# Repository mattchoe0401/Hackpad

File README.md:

# Hackpad
This Hackpad uses 7 keys and a rotary encoder, each programmed for different functions.

It has an OLED screen that uses global WPM (tracked by a background Python program) to determine when a Bongo Cat hits.

The keybinds are as follows:

COPY&nbsp;&nbsp;&emsp;PASTE&emsp;&nbsp;&nbsp;UP&emsp;&emsp;&emsp;&nbsp;MUTE\
CUT&emsp;&emsp;LEFT&emsp;&emsp;&nbsp;DOWN&emsp;&nbsp;&nbsp;RIGHT

Pressing down the rotary encoder mutes/unmutes, while rotating it adjusts the volume.

# CAD Model

# Schematic and PCB
Schematic:\

PCB:\

# Bill of Materials
**See hackpad_bom.csv for the list of prices and links**
- 1x Seeed XIAO RP2040
- 7x Cherry MX key switches
- 5x M3x16mm screws
- 5x M3x5mx4mm heatset inserts
- 1x EC11E rotary encoder
- 1x 0.91-inch OLED display
- 7x White DSA keycaps

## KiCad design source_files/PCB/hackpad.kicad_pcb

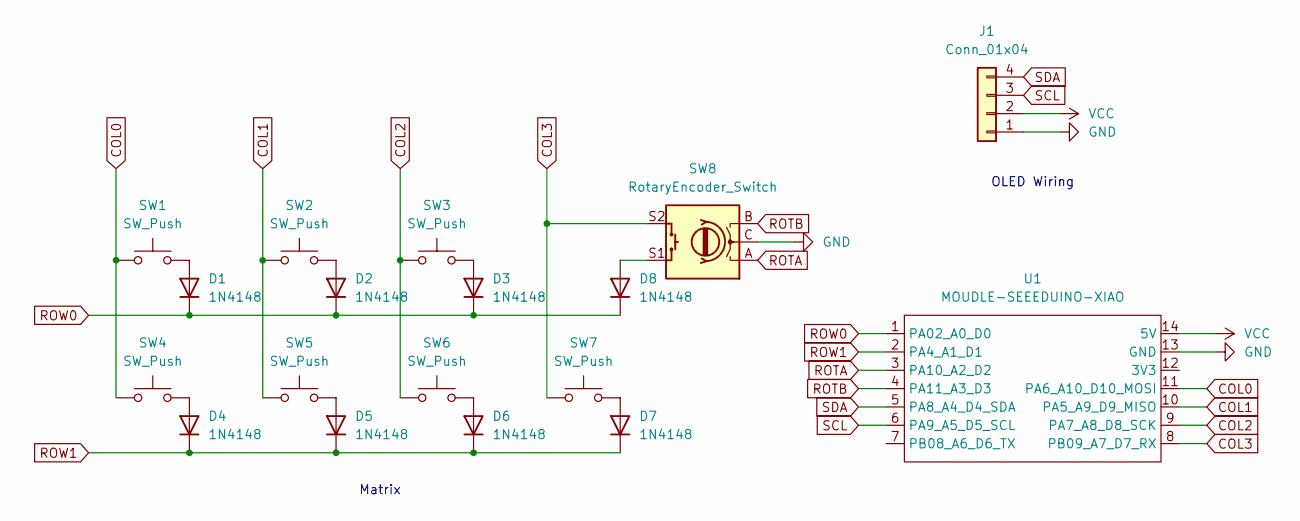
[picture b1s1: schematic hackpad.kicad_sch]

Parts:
D1, D2, D3, D4, D5, D6, D7, D8: 1N4148; D_DO-35_SOD27_P7.62mm_Horizontal
J1: Conn_01x04; SSD1306-0.91-OLED-4pin-128x32
SW1, SW2, SW3, SW4, SW5, SW6, SW7: SW_Push; SW_Cherry_MX_1.00u_PCB
SW8: RotaryEncoder_Switch; RotaryEncoder_Alps_EC11E-Switch_Vertical_H20mm
U1: MOUDLE-SEEEDUINO-XIAO; XIAO-Generic-Hybrid-14P-2.54-21X17.8MM

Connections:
COL0: SW1.1, SW4.1, U1.11 (PA6_A10_D10_MOSI)
COL1: SW2.1, SW5.1, U1.10 (PA5_A9_D9_MISO)
COL2: SW3.1, SW6.1, U1.9 (PA7_A8_D8_SCK)
COL3: SW7.1, SW8.S2, U1.8 (PB09_A7_D7_RX)
GND: J1.1, SW8.C, U1.13 (GND)
unnamed: D1.2 (A), SW1.2
unnamed: D2.2 (A), SW2.2
unnamed: D3.2 (A), SW3.2
unnamed: D4.2 (A), SW4.2
unnamed: D5.2 (A), SW5.2
unnamed: D6.2 (A), SW6.2
unnamed: D7.2 (A), SW7.2
unnamed: D8.2 (A), SW8.S1
ROTA: SW8.A, U1.3 (PA10_A2_D2)
ROTB: SW8.B, U1.4 (PA11_A3_D3)
ROW0: D1.1 (K), D2.1 (K), D3.1 (K), D8.1 (K), U1.1 (PA02_A0_D0)
ROW1: D4.1 (K), D5.1 (K), D6.1 (K), D7.1 (K), U1.2 (PA4_A1_D1)
SCL: J1.3, U1.6 (PA9_A5_D5_SCL)
SDA: J1.4, U1.5 (PA8_A4_D4_SDA)
VCC: J1.2, U1.14 (5V)

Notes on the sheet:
Matrix
OLED Wiring

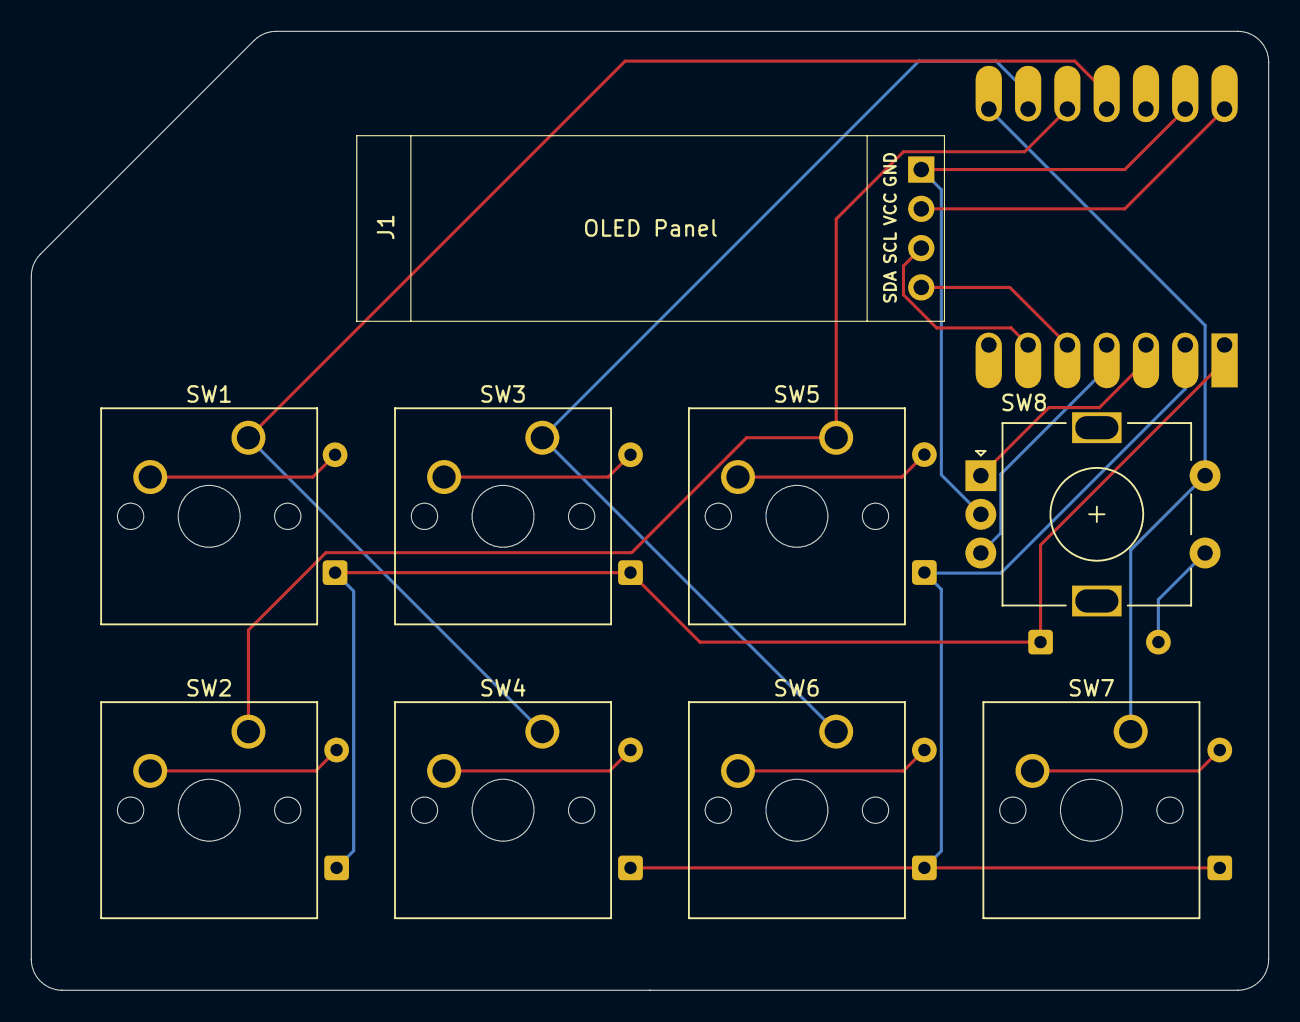
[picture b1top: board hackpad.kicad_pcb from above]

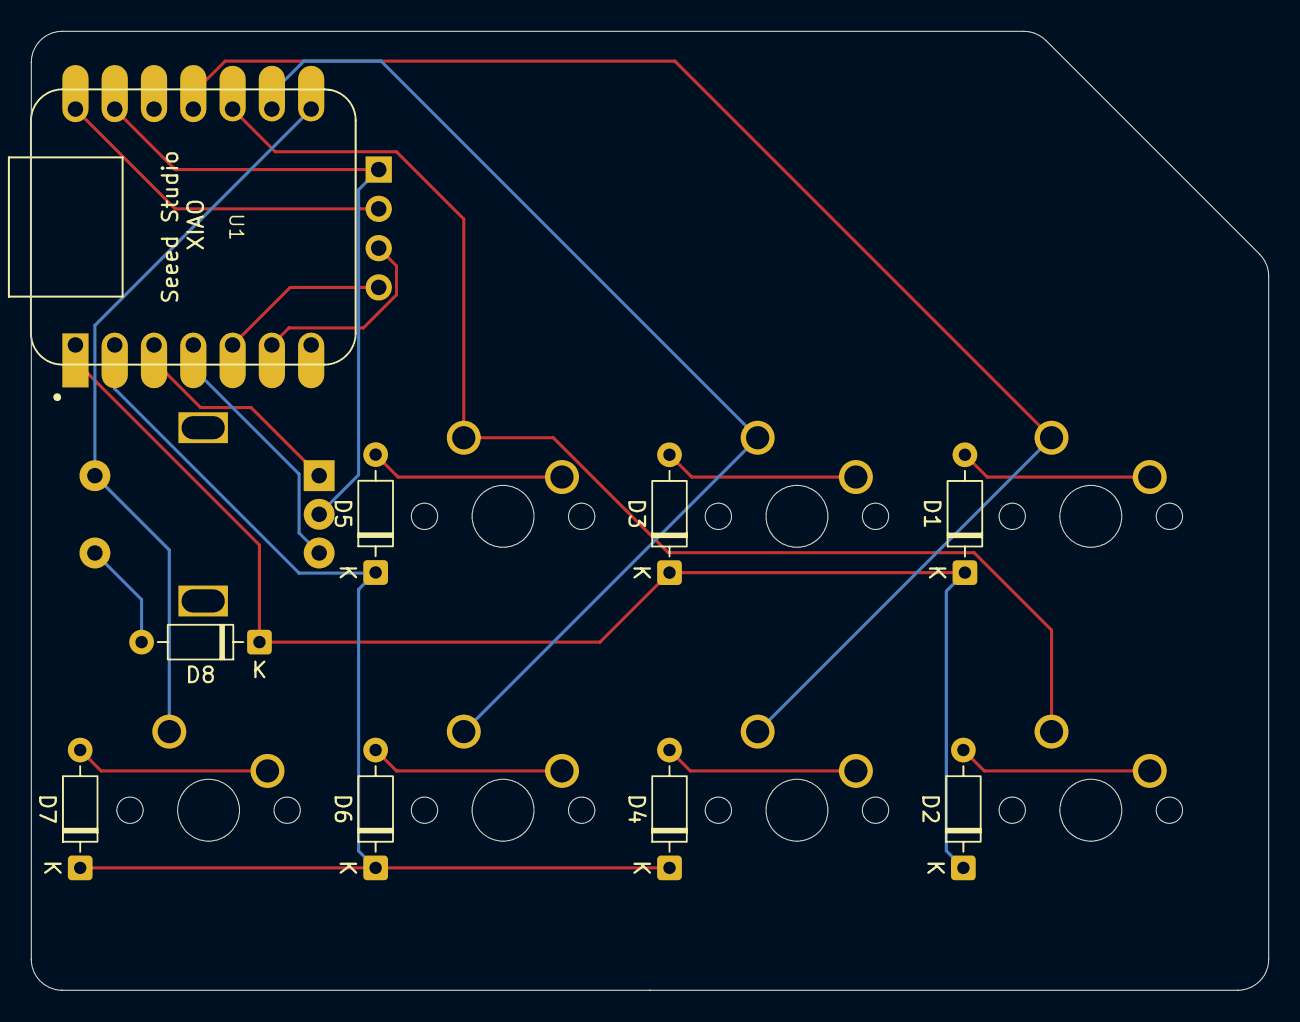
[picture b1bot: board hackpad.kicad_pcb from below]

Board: 2 copper layers, 80.0 x 62.0 mm, 18 parts (9 on the bottom side), 20 nets.
